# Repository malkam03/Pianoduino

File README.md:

# Pianoduino
A 61 key MIDI keyboard project with Arduino and some parts of a broken Yamaha PSR-E303. With control knobs, buttons, LCD and resistive panel. 

## Getting Started
Since this is a hardware and software project, these instructions will get you a copy of the project up and running on your device for development and testing purposes.  

### Prerequisites

**Arduino Circuit**
First you need to build the [circuit](PCB/Pianoduino/Mainboard.brd) if you have a Yamaha PSR-E303, or you can modify it to fit your keys circuit.

**Arduino IDE** to edit and upload your code.
You can find the instructions of installation on the Arduino's [page](https://www.arduino.cc/en/Main/Software) depending on your operative system.

**Autodesk Eagle** to edit the circuit.
You can find the instructions of installation on the autodesk's [page](https://www.autodesk.com/products/eagle/free-download) depending on your operative system.

## Deployment

Just upload your code to the arduino + circuit and play :musical_keyboard:.

## Author
* **Malcolm Davis** - *Initial work* - [Pianoduino](https://github.com/malkam03/Pianoduino)

See also the list of [contributors](https://github.com/malkam03/Pianoduino/contributors.md) who participated in this project.

## License

This project is licensed under the MIT License - see the [LICENSE.md](LICENSE.md) file for details.

## Acknowledgments

* [Brian Benchoff](https://hackaday.com/2012/11/28/turning-toy-pianos-into-midi-keyboards/)
* [dylanstout](http://www.instructables.com/id/Arduino-MIDI-Controller/)
* [cgmalantonio](http://www.instructables.com/id/Touch-Screen-Overlay-with-Arduino/)

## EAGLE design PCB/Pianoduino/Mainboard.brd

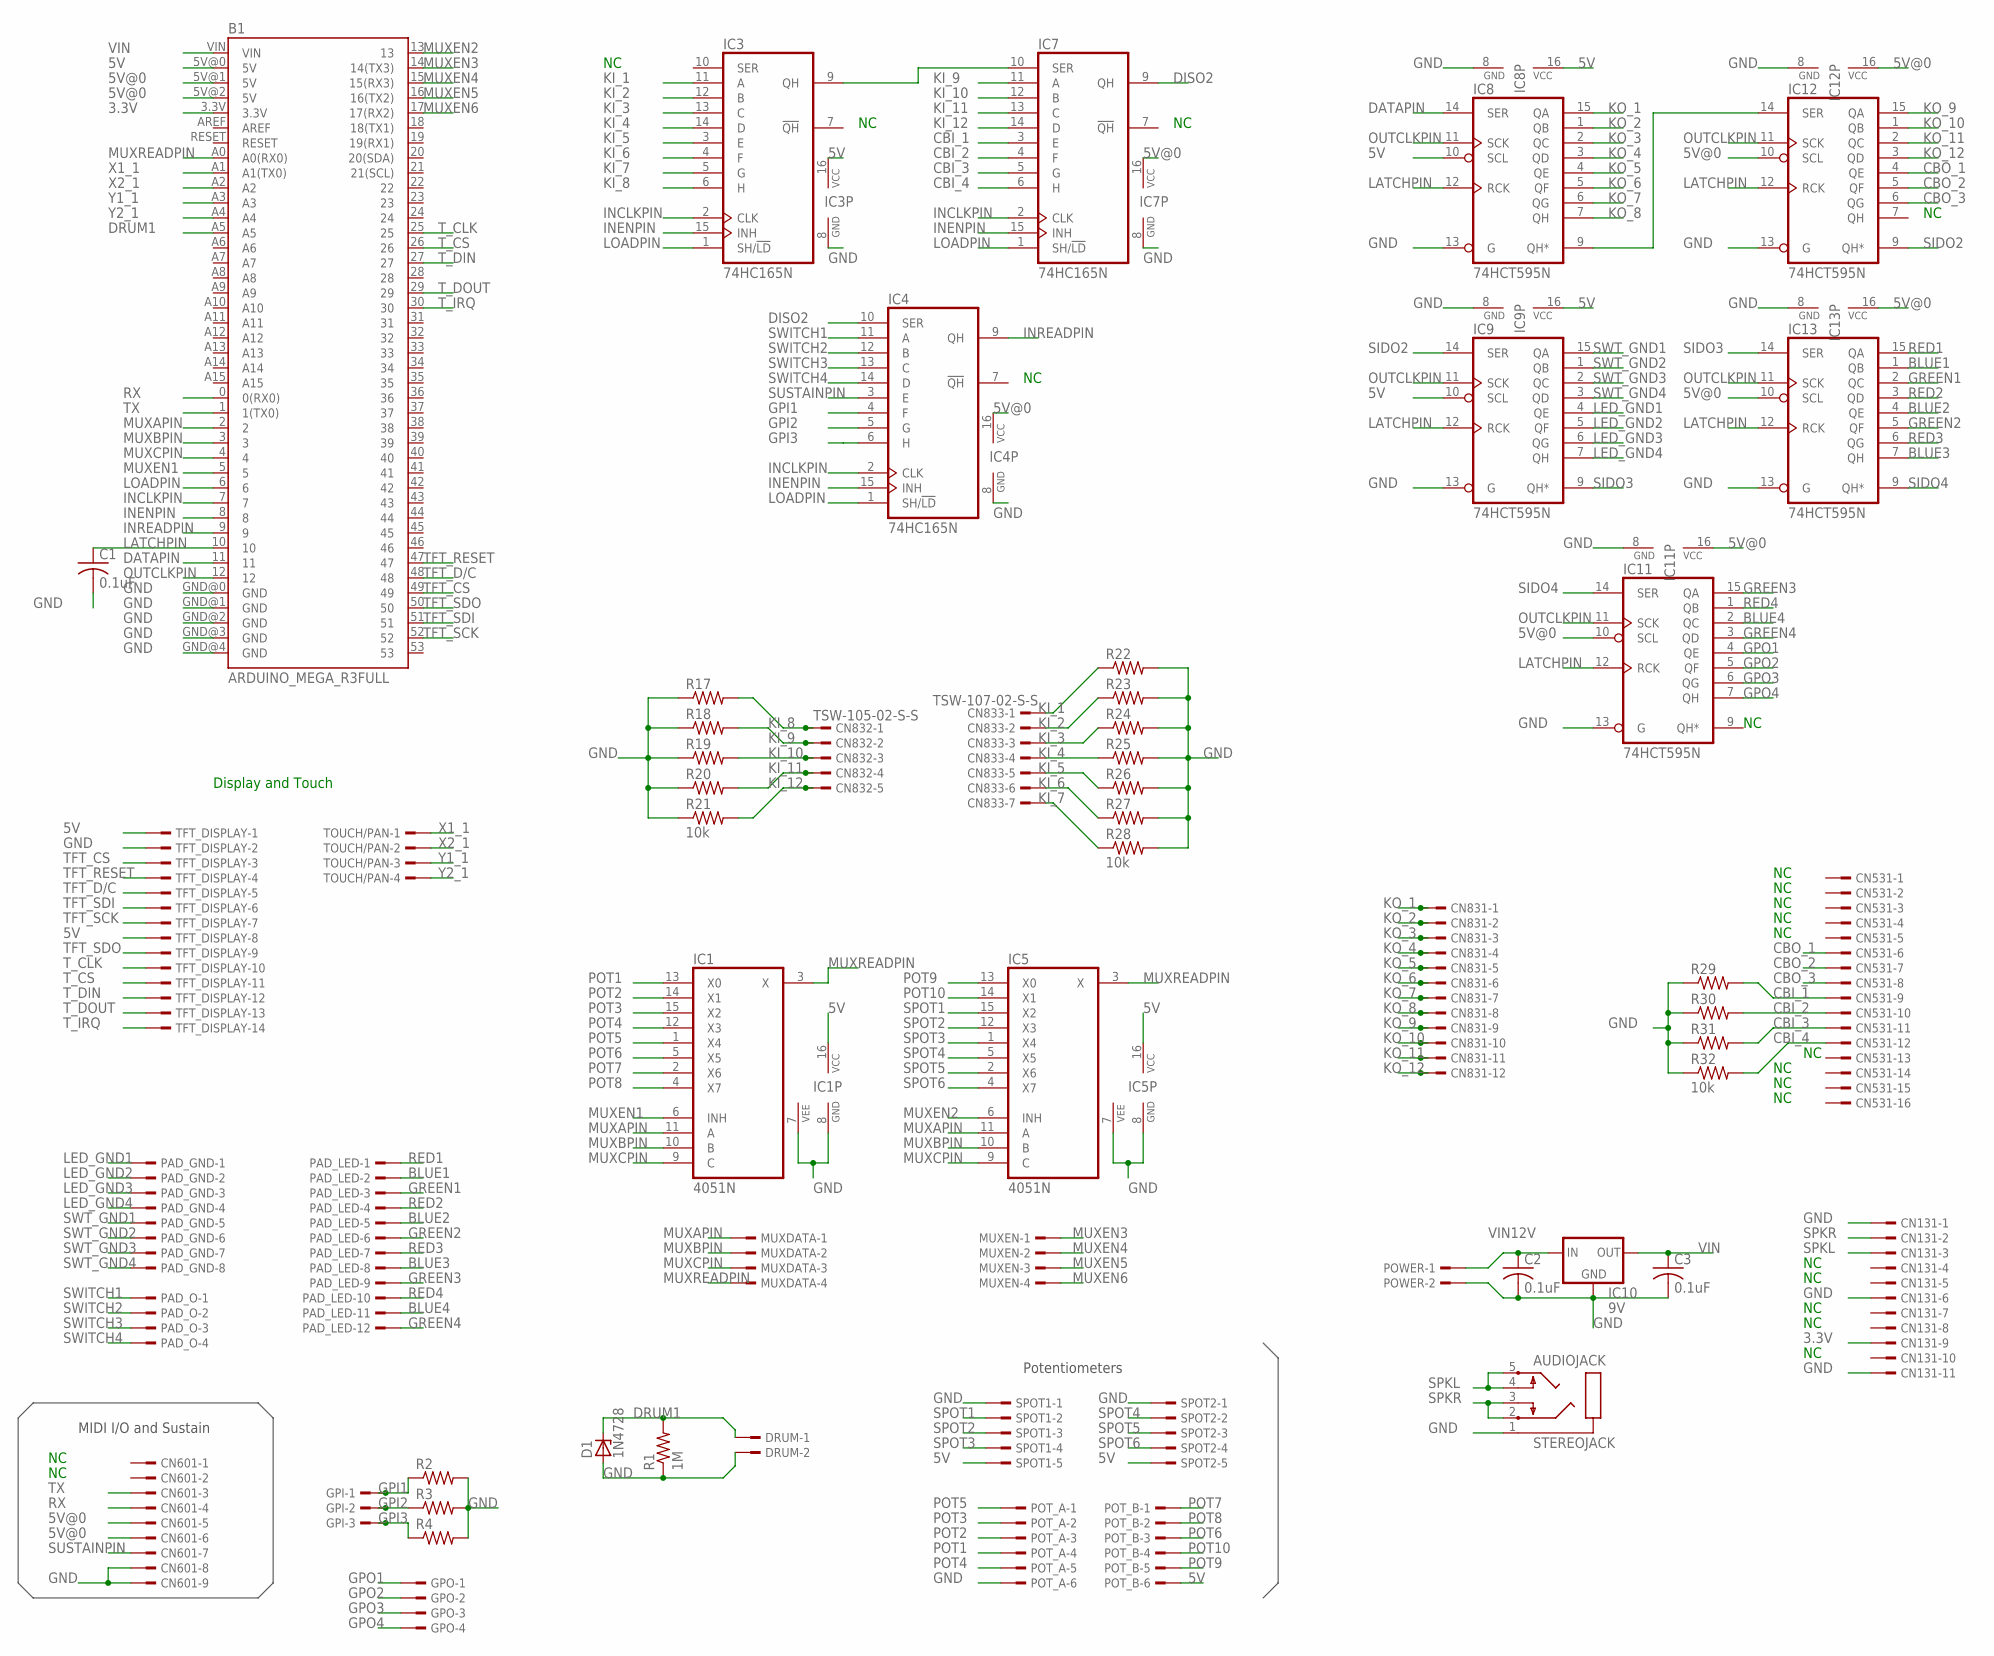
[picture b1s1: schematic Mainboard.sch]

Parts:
AUDIOJACK: STEREOJACK; STX3100
B1: ARDUINO_MEGA_R3FULL; ARDUINO_MEGA
C1, C2, C3: 0.1uF; C050-075X075
CN131: TSW-111-02-S-S
CN531: TSW-116-02-S-S
CN601: TSW-109-02-S-S
CN831: TSW-112-02-S-S
CN832: TSW-105-02-S-S
CN833: TSW-107-02-S-S
D1: 1N4728; DO41Z10
DRUM: TSW-102-02-S-S
GPI: TSW-103-02-S-S
GPO: TSW-104-02-S-S
IC1, IC5: 4051N; DIL16
IC3, IC4, IC7: 74HC165N; DIL16
IC8, IC9, IC11, IC12, IC13: 74HCT595N; DIL16
IC10: 9V; 78XXL
MUXDATA: TSW-104-02-S-S
MUXEN: TSW-104-02-S-S
PAD_GND: TSW-108-02-S-S
PAD_LED: TSW-112-02-S-S
PAD_O: TSW-104-02-S-S
POT_A: TSW-106-02-S-S
POT_B: TSW-106-02-S-S
POWER: TSW-102-02-S-S
R1: 1M; 0309/12
R2, R3, R4, R17, R18, R19, R20, R21, R22, R23, R24, R25, R26, R27, R28, R29, R30, R31, R32: 10k; 0309/12
SPOT1, SPOT2: TSW-105-02-S-S
TFT_DISPLAY: TSW-114-02-S-S
TOUCH/PAN: TSW-104-02-S-S

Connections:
3.3V: B1.3.3V, CN131.9
5V: B1.5V@0 (5V), IC1.16 (VCC), IC3.16 (VCC), IC5.16 (VCC), IC8.10 (SCL), IC8.16 (VCC), IC9.10 (SCL), IC9.16 (VCC), POT_B.6, SPOT1.5, SPOT2.5, TFT_DISPLAY.1, TFT_DISPLAY.8
5V@0: B1.5V@1 (5V), B1.5V@2 (5V), CN601.5, CN601.6, IC4.16 (VCC), IC7.16 (VCC), IC11.10 (SCL), IC11.16 (VCC), IC12.10 (SCL), IC12.16 (VCC), IC13.10 (SCL), IC13.16 (VCC)
BLUE1: IC13.1 (QB), PAD_LED.2
BLUE2: IC13.4 (QE), PAD_LED.5
BLUE3: IC13.7 (QH), PAD_LED.8
BLUE4: IC11.2 (QC), PAD_LED.11
CBI_1: CN531.9, IC7.3 (E), R29.2
CBI_2: CN531.10, IC7.4 (F), R30.2
CBI_3: CN531.11, IC7.5 (G), R31.2
CBI_4: CN531.12, IC7.6 (H), R32.2
CBO_1: CN531.6, IC12.4 (QE)
CBO_2: CN531.7, IC12.5 (QF)
CBO_3: CN531.8, IC12.6 (QG)
DATAPIN: B1.11, IC8.14 (SER)
DISO1: IC3.9 (QH), IC7.10 (SER)
DISO2: IC4.10 (SER), IC7.9 (QH)
DRUM1: B1.A5, D1.C, DRUM.1, R1.2
GND: AUDIOJACK.1, B1.GND@0 (GND), B1.GND@1 (GND), B1.GND@2 (GND), B1.GND@3 (GND), B1.GND@4 (GND), C1.2, C2.2, C3.2, CN131.1, CN131.6, CN131.11, CN601.8, CN601.9, D1.A, DRUM.2, IC1.7 (VEE), IC1.8 (GND), IC3.8 (GND), IC4.8 (GND), IC5.7 (VEE), IC5.8 (GND), IC7.8 (GND), IC8.8 (GND), IC8.13 (G), IC9.8 (GND), IC9.13 (G), IC10.GND, IC11.8 (GND), IC11.13 (G), IC12.8 (GND), IC12.13 (G), IC13.8 (GND), IC13.13 (G), POT_A.6, POWER.2, R1.1, R2.2, R3.2, R4.2, R17.1, R18.1, R19.1, R20.1, R21.1, R22.2, R23.2, R24.2, R25.2, R26.2, R27.2, R28.2, R29.1, R30.1, R31.1, R32.1, SPOT1.1, SPOT2.1, TFT_DISPLAY.2
GPI1: GPI.1, IC4.4 (F), R2.1
GPI2: GPI.2, IC4.5 (G), R3.1
GPI3: GPI.3, IC4.6 (H), R4.1
GPO1: GPO.1, IC11.4 (QE)
GPO2: GPO.2, IC11.5 (QF)
GPO3: GPO.3, IC11.6 (QG)
GPO4: GPO.4, IC11.7 (QH)
GREEN1: IC13.2 (QC), PAD_LED.3
GREEN2: IC13.5 (QF), PAD_LED.6
GREEN3: IC11.15 (QA), PAD_LED.9
GREEN4: IC11.3 (QD), PAD_LED.12
INCLKPIN: B1.7, IC3.2 (CLK), IC4.2 (CLK), IC7.2 (CLK)
INENPIN: B1.8, IC3.15 (INH), IC4.15 (INH), IC7.15 (INH)
INREADPIN: B1.9, IC4.9 (QH)
KI_1: CN833.1, IC3.11 (A), R22.1
KI_2: CN833.2, IC3.12 (B), R23.1
KI_3: CN833.3, IC3.13 (C), R24.1
KI_4: CN833.4, IC3.14 (D), R25.1
KI_5: CN833.5, IC3.3 (E), R26.1
KI_6: CN833.6, IC3.4 (F), R27.1
KI_7: CN833.7, IC3.5 (G), R28.1
KI_8: CN832.1, IC3.6 (H), R17.2
KI_9: CN832.2, IC7.11 (A), R18.2
KI_10: CN832.3, IC7.12 (B), R19.2
KI_11: CN832.4, IC7.13 (C), R20.2
KI_12: CN832.5, IC7.14 (D), R21.2
KO_1: CN831.1, IC8.15 (QA)
KO_2: CN831.2, IC8.1 (QB)
KO_3: CN831.3, IC8.2 (QC)
KO_4: CN831.4, IC8.3 (QD)
KO_5: CN831.5, IC8.4 (QE)
KO_6: CN831.6, IC8.5 (QF)
KO_7: CN831.7, IC8.6 (QG)
KO_8: CN831.8, IC8.7 (QH)
KO_9: CN831.9, IC12.15 (QA)
KO_10: CN831.10, IC12.1 (QB)
KO_11: CN831.11, IC12.2 (QC)
KO_12: CN831.12, IC12.3 (QD)
LATCHPIN: B1.10, C1.1, IC8.12 (RCK), IC9.12 (RCK), IC11.12 (RCK), IC12.12 (RCK), IC13.12 (RCK)
LED_GND1: IC9.4 (QE), PAD_GND.1
LED_GND2: IC9.5 (QF), PAD_GND.2
LED_GND3: IC9.6 (QG), PAD_GND.3
LED_GND4: IC9.7 (QH), PAD_GND.4
LOADPIN: B1.6, IC3.1 (SH/!LD), IC4.1 (SH/!LD), IC7.1 (SH/!LD)
MUXAPIN: B1.2, IC1.11 (A), IC5.11 (A), MUXDATA.1
MUXBPIN: B1.3, IC1.10 (B), IC5.10 (B), MUXDATA.2
MUXCPIN: B1.4, IC1.9 (C), IC5.9 (C), MUXDATA.3
MUXEN1: B1.5, IC1.6 (INH)
MUXEN2: B1.13, IC5.6 (INH)
MUXEN3: B1.14 (14(TX3)), MUXEN.1
MUXEN4: B1.15 (15(RX3)), MUXEN.2
MUXEN5: B1.16 (16(TX2)), MUXEN.3
MUXEN6: B1.17 (17(RX2)), MUXEN.4
MUXREADPIN: B1.A0 (A0(RX0)), IC1.3 (X), IC5.3 (X), MUXDATA.4
unnamed: IC8.9 (QH*), IC12.14 (SER)
OUTCLKPIN: B1.12, IC8.11 (SCK), IC9.11 (SCK), IC11.11 (SCK), IC12.11 (SCK), IC13.11 (SCK)
POT1: IC1.13 (X0), POT_A.4
POT2: IC1.14 (X1), POT_A.3
POT3: IC1.15 (X2), POT_A.2
POT4: IC1.12 (X3), POT_A.5
POT5: IC1.1 (X4), POT_A.1
POT6: IC1.5 (X5), POT_B.3
POT7: IC1.2 (X6), POT_B.1
POT8: IC1.4 (X7), POT_B.2
POT9: IC5.13 (X0), POT_B.5
POT10: IC5.14 (X1), POT_B.4
RED1: IC13.15 (QA), PAD_LED.1
RED2: IC13.3 (QD), PAD_LED.4
RED3: IC13.6 (QG), PAD_LED.7
RED4: IC11.1 (QB), PAD_LED.10
RX: B1.0 (0(RX0)), CN601.4
SIDO2: IC9.14 (SER), IC12.9 (QH*)
SIDO3: IC9.9 (QH*), IC13.14 (SER)
SIDO4: IC11.14 (SER), IC13.9 (QH*)
SPKL: AUDIOJACK.4, AUDIOJACK.5, CN131.3
SPKR: AUDIOJACK.2, AUDIOJACK.3, CN131.2
SPOT1: IC5.15 (X2), SPOT1.2
SPOT2: IC5.12 (X3), SPOT1.3
SPOT3: IC5.1 (X4), SPOT1.4
SPOT4: IC5.5 (X5), SPOT2.2
SPOT5: IC5.2 (X6), SPOT2.3
SPOT6: IC5.4 (X7), SPOT2.4
SUSTAINPIN: CN601.7, IC4.3 (E)
SWITCH1: IC4.11 (A), PAD_O.1
SWITCH2: IC4.12 (B), PAD_O.2
SWITCH3: IC4.13 (C), PAD_O.3
SWITCH4: IC4.14 (D), PAD_O.4
SWT_GND1: IC9.15 (QA), PAD_GND.5
SWT_GND2: IC9.1 (QB), PAD_GND.6
SWT_GND3: IC9.2 (QC), PAD_GND.7
SWT_GND4: IC9.3 (QD), PAD_GND.8
TFT_CS: B1.49, TFT_DISPLAY.3
TFT_D/C: B1.48, TFT_DISPLAY.5
TFT_RESET: B1.47, TFT_DISPLAY.4
TFT_SCK: B1.52, TFT_DISPLAY.7
TFT_SDI: B1.51, TFT_DISPLAY.6
TFT_SDO: B1.50, TFT_DISPLAY.9
TX: B1.1 (1(TX0)), CN601.3
T_CLK: B1.25, TFT_DISPLAY.10
T_CS: B1.26, TFT_DISPLAY.11
T_DIN: B1.27, TFT_DISPLAY.12
T_DOUT: B1.29, TFT_DISPLAY.13
T_IRQ: B1.30, TFT_DISPLAY.14
VIN: B1.VIN, C3.1, IC10.OUT
VIN12V: C2.1, IC10.IN, POWER.1
X1_1: B1.A1 (A1(TX0)), TOUCH/PAN.1
X2_1: B1.A2, TOUCH/PAN.2
Y1_1: B1.A3, TOUCH/PAN.3
Y2_1: B1.A4, TOUCH/PAN.4

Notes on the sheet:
MIDI I/O and Sustain
Potentiometers
Display and Touch

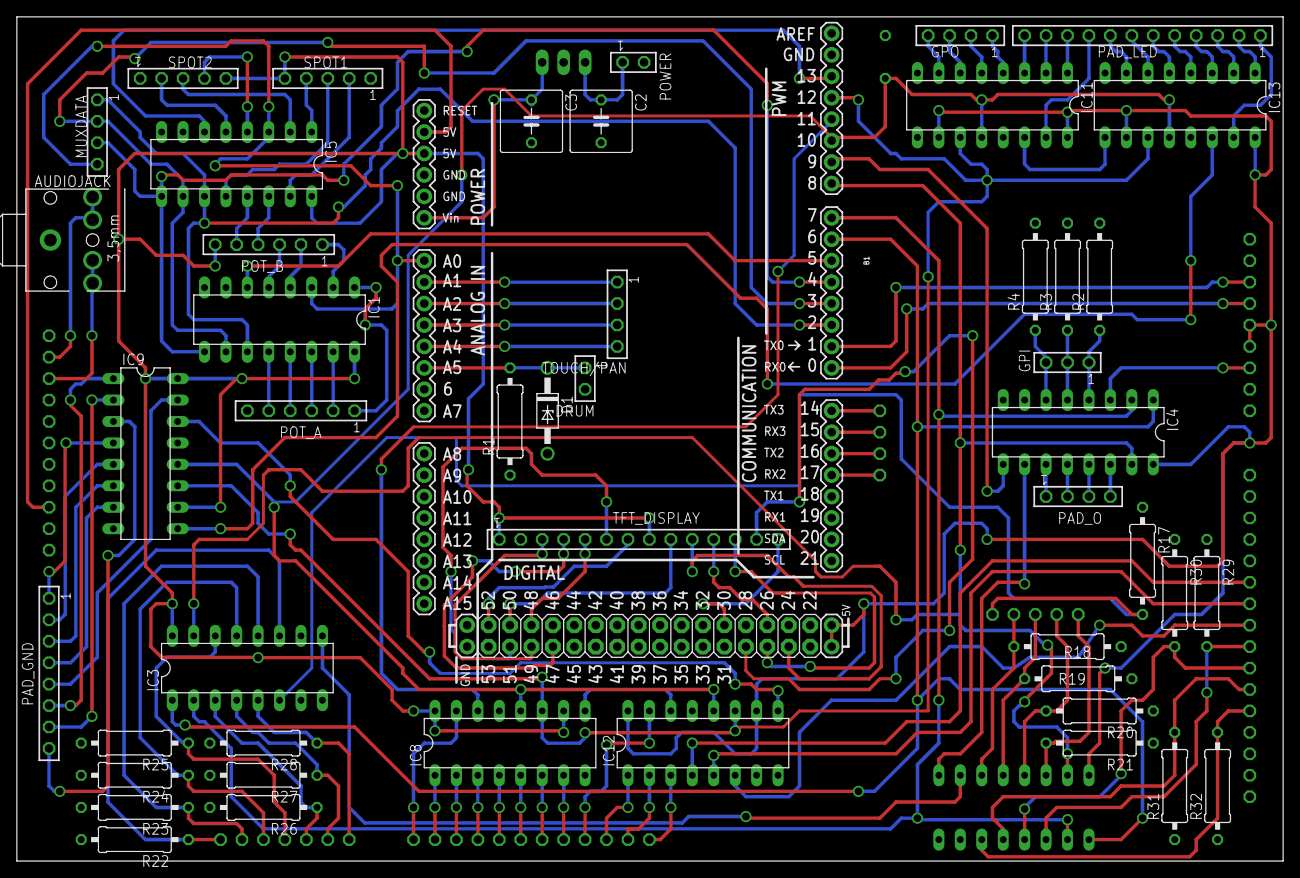
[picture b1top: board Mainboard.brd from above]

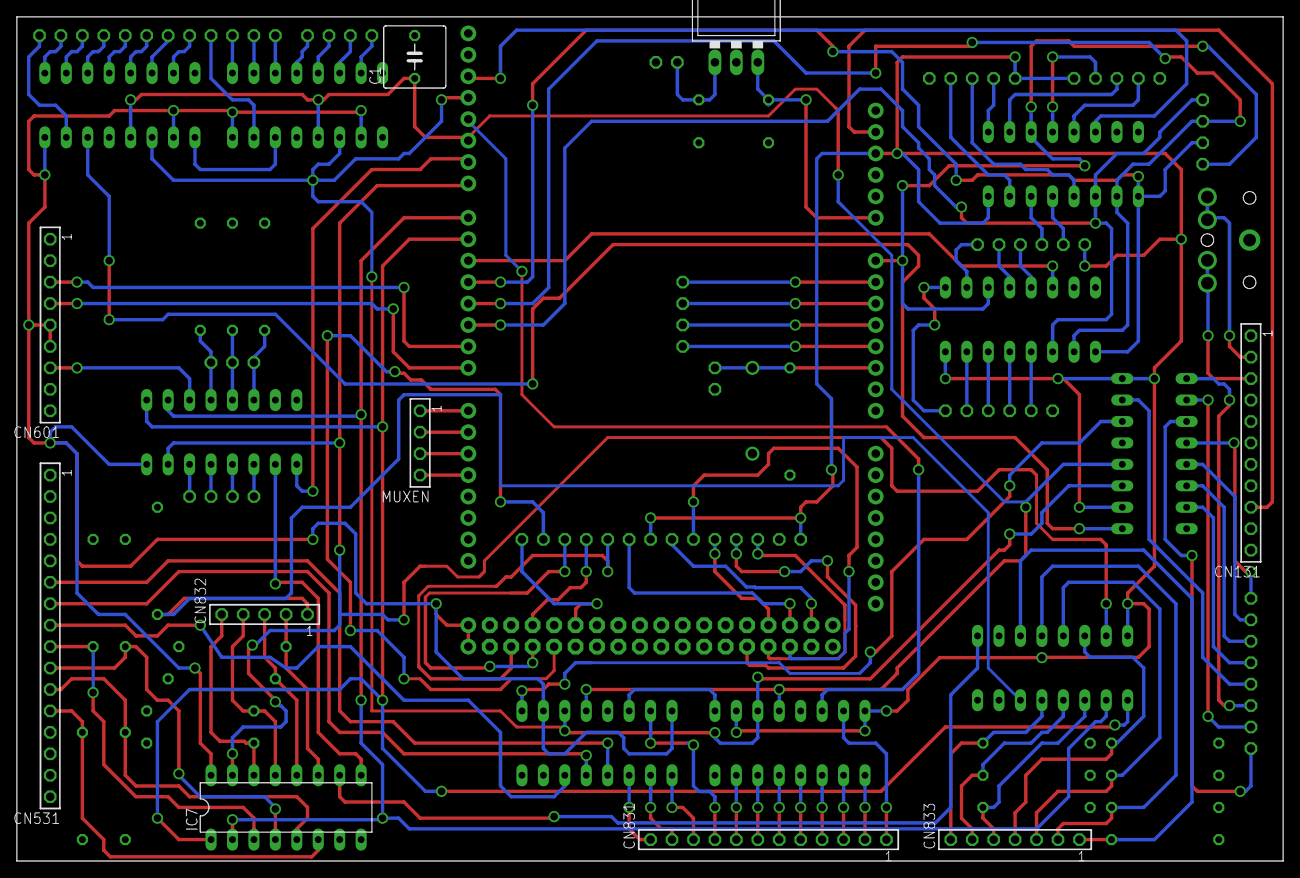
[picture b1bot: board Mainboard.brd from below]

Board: 2 copper layers, 150.0 x 100.0 mm, 58 parts (10 on the bottom side), 128 nets.

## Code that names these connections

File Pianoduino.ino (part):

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 */

//*********************Arduino Pins*************************//
static const byte muxAPin = 2;
static const byte muxBPin = 3;
static const byte muxCPin = 4;
static const byte muxReadPin = A0;
static const byte inClkPin = 7; //Shift in clock
static const byte loadPin = 6; //Shift in or load input. When high data, shifted. When Low data is loaded from parallel inputs.
static const byte inEnPin = 8; //Active low
static const byte inReadPin = 9;
static const byte dataPin = 11;
static const byte outClkPin = 12;
static const byte latchPin = 10;
//If a Analog mux is added, just connect the control pins in parallel and add the En pin to the list.
static const byte muxEn [] = {
  5};
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#ifdef debug 
  Serial.println("Setup Start");
#endif
  pinMode(muxAPin, OUTPUT);
  pinMode(muxBPin, OUTPUT);
  pinMode(muxCPin, OUTPUT);
  pinMode(inClkPin, OUTPUT);
  pinMode(loadPin, OUTPUT);
  pinMode(inEnPin, OUTPUT);
  pinMode(inReadPin, INPUT);
  pinMode(dataPin, OUTPUT);
  pinMode(latchPin, OUTPUT);
  pinMode(outClkPin, OUTPUT);
  //Set the enabler pins to outputs.
  for (i = 0; i < sizeof(muxEn) / sizeof(int); i++) {
    pinMode(muxEn[i], OUTPUT);
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
  readAnalog(); //Read the initial value of the knobs
  transpose(trans); //Set the octave to the initial value.
  digitalWrite(loadPin, HIGH); //On HIGH is read ready
  delay(1000); //Waits a second.
#ifdef debug 
  Serial.println("Setup Ready");
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    }
  }
  digitalWrite(pMuxEn, LOW);
  digitalWrite(muxAPin, sValue[0]);
  digitalWrite(muxBPin, sValue[1]);
  digitalWrite(muxCPin, sValue[2]);
}

/**
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  Serial.println(pColumn);
  delay(10);
#endif
  digitalWrite(latchPin, LOW);
  if (pColumn < 8) {
    shiftOut(dataPin, outClkPin, MSBFIRST, mask[pColumn]);
    shiftOut(dataPin, outClkPin, MSBFIRST, blank);
    shiftOut(dataPin, outClkPin, MSBFIRST, mask[pColumn]);
  } 
  else {
    shiftOut(dataPin, outClkPin, MSBFIRST, mask[pColumn % 8]);
    shiftOut(dataPin, outClkPin, MSBFIRST, mask[pColumn % 8]);
    shiftOut(dataPin, outClkPin, MSBFIRST, blank);
  }
  digitalWrite(latchPin, HIGH);
#ifdef debug 
  Serial.println("Shift done.");
#endif
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  for (byte i = 0; i < sizeof(muxEn) / sizeof(byte); i++) {
    for (byte y = 0; y < 8; y++) {
      muxToPin(y, muxEn[i]);
      tmp = map(analogRead(muxReadPin), 0, 1023, 0, 127);
      if (i * 8 + y < 15) {
        //If the value is greater or smaller than the actual value plus or minus the threshold send the change value.
        if (tmp > analogValue[i * 8 + y] + analogThreshold || tmp < analogValue[i * 8 + y] - analogThreshold  ) {
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#ifdef debug 
  Serial.println("Scanning rows start");
  Serial.print("Load pin: ");
  Serial.println(loadPin);
  Serial.print("inEnPin pin: ");
  Serial.println(inEnPin);
  Serial.print("inReadPin pin: ");
  Serial.println(inReadPin);
  delay(10);
#endif
  digitalWrite(loadPin, LOW); //On Low the parallel data is collected
  delayMicroseconds(5);
  digitalWrite(loadPin, HIGH); //On HIGH is read ready
  delayMicroseconds(5);
  digitalWrite(inEnPin, LOW); //Active Low
  shiftIn(inReadPin, inClkPin);
  digitalWrite(inEnPin, HIGH); //Active Low
#ifdef debug 
  Serial.println("Scanning rows end");
  delay(1);
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#endif
  for (short i = shiftIns - 1; i >= 0 ; i--)
  {
    digitalWrite(inClkPin, LOW);
    delayMicroseconds(5);
    rowsRead[i] = digitalRead(inReadPin);
    digitalWrite(inClkPin, HIGH);
  }
#ifdef debug
  Serial.println("ShiftIn End");
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
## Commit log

2017-02-06 First working version of the arduino code.
2017-02-12 Ghost notes that triggers inbetween the two switches, and velocity sensitivity added. Also the F# and G notes codes where added, so as a debug flag for some tests.
2017-02-21 Octave transposition method implemented, analog mux read methods added, to read the knobs values and the drums. Some ints where replaced by bytes to save space. Debug prints added to test some errors.
2017-02-22 Space added.
2017-02-25 MMidi message, on, off and control methods added or refactored and keyboard and drums channels added so the keyboard can send different notes through different channels.
2017-03-10 Added readAnalog, readButtons, readKey and other aux methods to implemment the knobs and buttons functions. Also some control variables and constants were added. The debug code has been modified.
2017-04-14 Schematic and pcb designd added, 3D model added.
2017-04-14 Readme and license fixed.
2017-05-28 Compile error fixed, fine tuning analogReads.
2017-05-29 Controller pad methods added.
2017-07-06 LICENSE file extention fixed, and markdown added. Images moved to a renderings directory.
2017-07-07 Readm e file updated. And the images was fixed.
2017-08-28 License changed from GPL to MIT.
2017-08-28 Readme project image replaced.
2017-08-29 Stand added and some carpet too.
2017-08-29 More pictures of the concept added.
2017-08-29 Ableton presets added.

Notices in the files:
parts and their libraries:
SparkFun-Boards1: Licensing: Creative Commons ShareAlike 4.0 International - https://creativecommons.org/licenses/by-sa/4.0
